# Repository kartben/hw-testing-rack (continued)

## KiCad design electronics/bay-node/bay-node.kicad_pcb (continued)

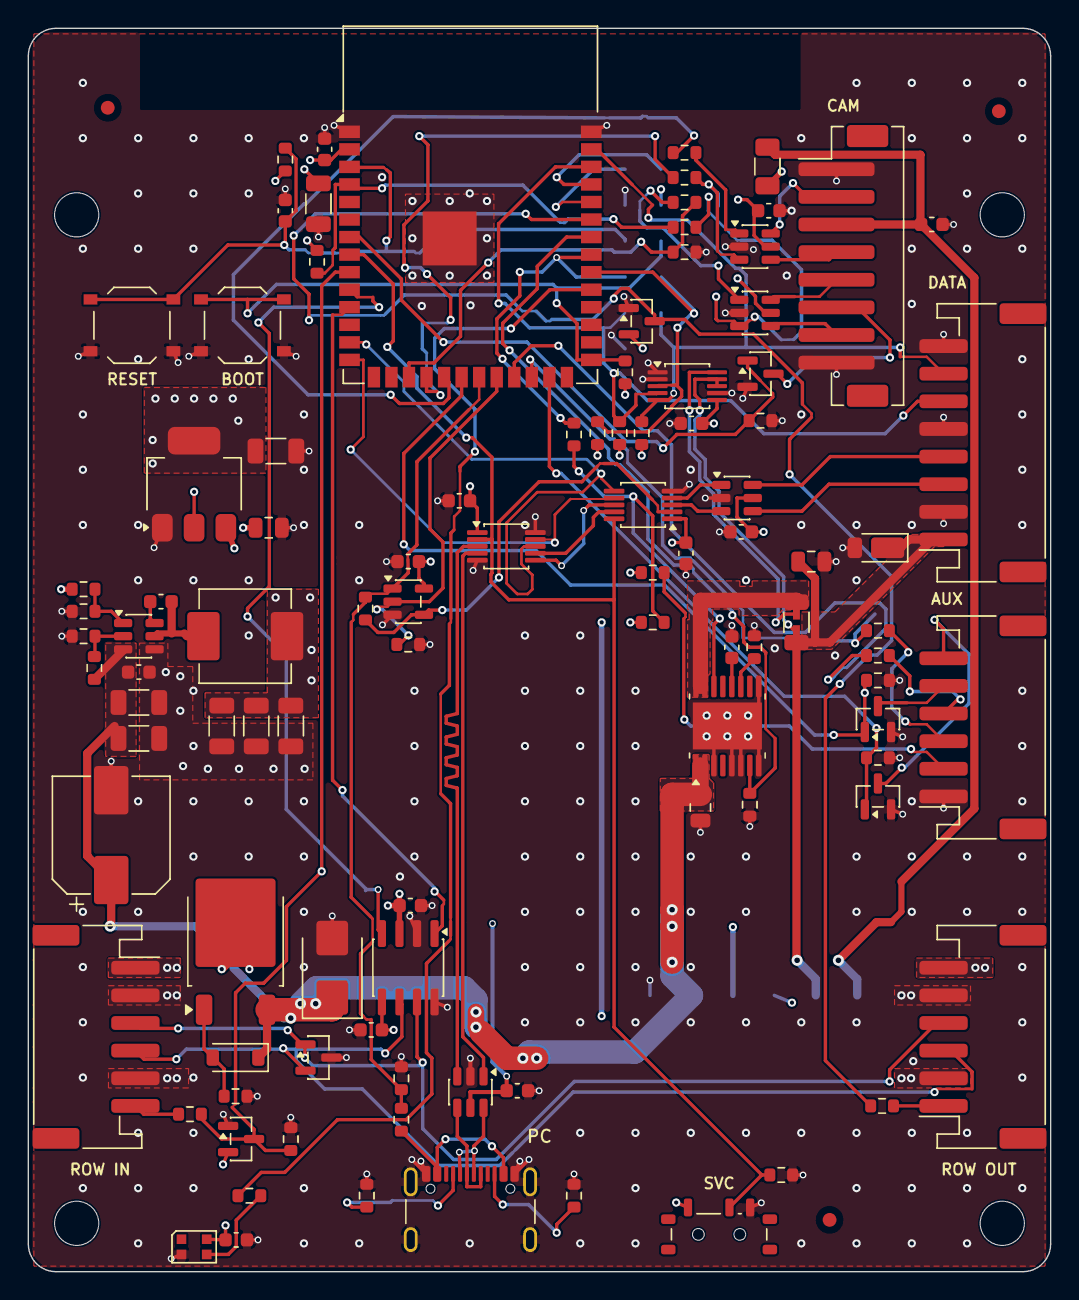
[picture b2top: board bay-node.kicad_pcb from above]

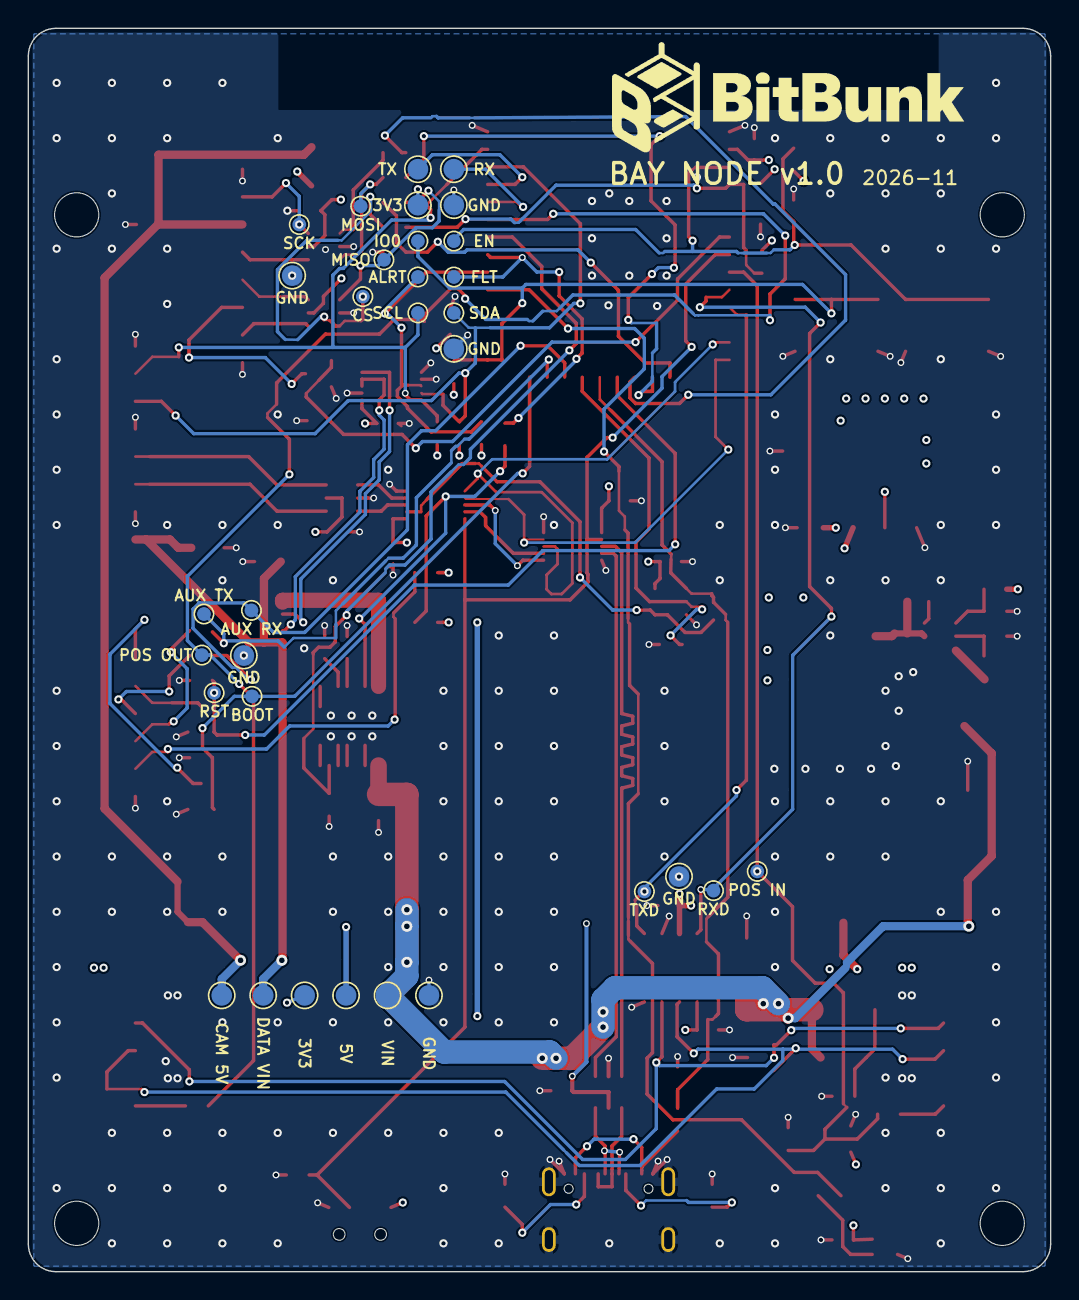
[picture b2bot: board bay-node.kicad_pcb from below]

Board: 4 copper layers, 74.0 x 90.0 mm, 139 parts (32 on the bottom side), 79 nets.

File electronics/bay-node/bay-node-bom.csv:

Designator,Qty,Value,Footprint,MPN,Manufacturer,LCSC,Description,DNP,Alternative,Assembly
C1,1,100u/50V,CP_Elec_8x10,RVT1H101M0810,Honor Elec,C3352,100 µF 50 V aluminium electrolytic,,,
"C2,C3",2,10u,C_1206_3216Metric,CL31A106KBHNNNE,Samsung Electro-Mechanics,C13585,Capacitor 10u 1206,,,
"C4,C5,C14,C16,C17,C18,C19,C22,C23,C24,C25,C26,C27,C28",14,100n,C_0603_1608Metric,CC0603KRX7R9BB104,YAGEO,C14663,Capacitor 100n 0603,,,
"C7,C8,C9,C12,C13",5,22u,C_1206_3216Metric,CL31A226KAHNNNE,Samsung Electro-Mechanics,C12891,Capacitor 22u 1206,,,
C11,1,10u,C_0805_2012Metric,CL21A106KAYNNNE,Samsung Electro-Mechanics,C15850,Capacitor 10u 0805,,,
C15,1,1u,C_0603_1608Metric,CL10A105KB8NNNC,Samsung Electro-Mechanics,C15849,Capacitor 1u 0603,,,
"C20,C21",2,1u,C_0805_2012Metric,CL21B105KBFNNNE,Samsung Electro-Mechanics,C28323,Capacitor 1u 0805,,,
C29,1,22n,C_0603_1608Metric,CL10B223KB8NNNC,Samsung Electro-Mechanics,C21122,Capacitor 22n 0603,,,
D1,1,BZT52C12,D_SOD-123,BZT52C12,CJ,C43491,"12 V zener, P-FET gate clamp",,,
D2,1,SMBJ33A,D_SMB,SMBJ33A,Brightking,C78419,"TVS 33 V stand-off, 600 W (unidirectional)",,,
D4,1,WS2812B-2020-V6,LED_WS2812B-2020_PLCC4_2.0x2.0mm,WS2812B-2020-V6,Worldsemi,C52917434,"addressable RGB LED, 3.3–5.3 V",,WS2812C-2020-V6 (C55109522) is Economic-PCBA capable; check its pinout before swapping,
D5,1,PESD2CAN,SOT-23,"PESD2CAN,215",Nexperia,C75176,"CAN bus ESD protection, 24 V stand-off",,,
"D6,D7",2,BAT54S,SOT-23,BAT54S,hongjiacheng,C7420333,dual Schottky in series: clamps a line to GND and +3V3,,,
D8,1,DFLS260-7,D_PowerDI-123,DFLS260-7,Diodes Inc.,C209346,"60 V 2 A Schottky, 0.62 V at 2 A",,,
F1,1,0.75A,Fuse_1206_3216Metric,SMD1206P075TF,RUILON,C20987,"PTC 0.75 A hold, 1.5 A trip, 1206",,,
J1,1,ROW IN,JST_PH_S6B-PH-SM4-TB_1x06-1MP_P2.00mm_Horizontal,S6B-PH-SM4-TB(LF)(SN),JST,C265405,"JST PH 6-pin, side entry, SMD",,,
J2,1,ROW OUT,JST_PH_S6B-PH-SM4-TB_1x06-1MP_P2.00mm_Horizontal,S6B-PH-SM4-TB(LF)(SN),JST,C265405,"JST PH 6-pin, side entry, SMD",,,
J3,1,PC,USB_C_Receptacle_GCT_USB4105-xx-A_16P_TopMnt_Horizontal,USB4105-GF-A-120,GCT,C5184243,"USB-C receptacle, USB 2.0, 16 pins, 5 A on VBUS",,,
J5,1,AUX,JST_PH_S6B-PH-SM4-TB_1x06-1MP_P2.00mm_Horizontal,S6B-PH-SM4-TB(LF)(SN),JST,C265405,"JST PH 6-pin, side entry, SMD",,,
J6,1,CAM,JST_PH_B8B-PH-SM4-TB_1x08-1MP_P2.00mm_Vertical,B8B-PH-SM4-TB(LF)(SN),JST,C495548,"JST PH 8-pin, vertical, SMD",,,
J7,1,DATA,JST_PH_S8B-PH-SM4-TB_1x08-1MP_P2.00mm_Horizontal,S8B-PH-SM4-TB(LF)(SN),JST,C265121,"JST PH 8-pin, side entry, SMD",,,
L1,1,4.7u,L_Changjiang_FXL0630,IHLP2525CZEK4R7M01,Vishay,C48009678,"4.7 µH, 75 V, 10 A sat (−20 %), 5.5 A heat (ΔT 40 °C), 37 mΩ (40 max), molded",,IHLP2525CZER4R7M01 (C553961): the same part on a 2000-piece reel,
Q1,1,SUD50P06-15(UMW),TO-252-2,SUD50P06-15(UMW),UMW,C7503186,"P-MOSFET 60 V, reverse-polarity protection",,"C7472883 (TECH PUBLIC), C141584 (Vishay)",
"Q2,Q3",2,2N7002,SOT-23,2N7002,CJ,C8545,N-MOSFET 60 V (open-drain AUX outputs),,,
Q4,1,AO3400A,SOT-23,AO3400A,Alpha & Omega Semicon,C20917,"N-MOSFET 30 V 5.7 A, 48 mΩ at 2.5 V (the camera light's low side)",,,
"R1,R2,R4,R13,R26,R27,R36,R39",8,100k,R_0603_1608Metric,0603WAF1003T5E,UNI-ROYAL(Uniroyal Elec),C25803,Resistor 100k 0603,,,
"R3,R6,R7,R11,R17,R18,R20,R28,R30,R37",10,10k,R_0603_1608Metric,0603WAF1002T5E,UNI-ROYAL(Uniroyal Elec),C25804,Resistor 10k 0603,,,
"R5,R12",2,18k,R_0603_1608Metric,0603WAF1802T5E,UNI-ROYAL(Uniroyal Elec),C25810,Resistor 18k 0603,,,
"R8,R31,R32,R33,R34",5,33,R_0603_1608Metric,0603WAF330JT5E,UNI-ROYAL(Uniroyal Elec),C23140,Resistor 33 0603,,,
"R9,R10",2,5.1k,R_0603_1608Metric,0603WAF5101T5E,UNI-ROYAL(Uniroyal Elec),C23186,Resistor 5.1k 0603,,,
R16,1,6.8k,R_0603_1608Metric,0603WAF6801T5E,UNI-ROYAL(Uniroyal Elec),C23212,Resistor 6.8k 0603,,,
R19,1,50m,R_1206_3216Metric_Kelvin,HoLR1206-1W-50mR-1%-75ppm,Milliohm,C601102,50 mΩ 1 % 1 W current shunt,,,
"R21,R22",2,2.2k,R_0603_1608Metric,0603WAF2201T5E,UNI-ROYAL(Uniroyal Elec),C4190,Resistor 2.2k 0603,,,
"R23,R24,R25,R43",4,1k,R_0603_1608Metric,0603WAF1001T5E,UNI-ROYAL(Uniroyal Elec),C21190,Resistor 1k 0603,,,
"R29,R42",2,150k,R_0603_1608Metric,0603WAF1503T5E,UNI-ROYAL(Uniroyal Elec),C22807,Resistor 150k 0603,,,
R35,1,680,R_0603_1608Metric,0603WAF6800T5E,UNI-ROYAL(Uniroyal Elec),C23228,Resistor 680 0603,yes,,
SW1,1,RESET,SW_Push_1P1T_XKB_TS-1187A,TS-1187A-B-A-B,XKB,C318884,tactile switch 5.1 × 5.1 mm,,,
SW2,1,BOOT,SW_Push_1P1T_XKB_TS-1187A,TS-1187A-B-A-B,XKB,C318884,tactile switch 5.1 × 5.1 mm,,,
SW3,1,SERVICE,SW_SPDT_Shouhan_MSK12C02,MSK12C02,SHOU HAN,C431540,"SPDT slide switch, side actuated",,,
U1,1,LMR51625YDDCR,TSOT-23-6,LMR51625YDDCR,Texas Instruments,C44991044,"4.3–60 V 2.5 A synchronous buck, 1.1 MHz, PFM + spread spectrum",,"LMR51625YFDDCR (C45262768): same, forced PWM, no spread spectrum; LMR51635YDDCR (C45262770): 3.5 A, 3.3 µH",
U2,1,AP2114H-3.3TRG1,SOT-223-3_TabPin2,AP2114H-3.3TRG1,Diodes Incorporated,C150716,"3.3 V 1 A LDO, 450 mV dropout at 1 A, SOT-223",,,
U3,1,ESP32-S3-WROOM-1-N8R8,ESP32-S3-WROOM-1_NoEPVias,ESP32-S3-WROOM-1-N8R8,Espressif,C2913201,"ESP32-S3 module, 8 MB flash, 8 MB octal PSRAM, PCB antenna, USB OTG (full speed)",,,
"U4,U8,U12,U13",4,USBLC6-2SC6,SOT-23-6,USBLC6-2SC6,STMicroelectronics,C7519,USB ESD protection,,C2687116 (UMW clone),
U5,1,MUX_PC,MSOP-10_3x3mm_P0.5mm,FSUSB42MUX,onsemi,C11355,USB 2.0 HS 2:1 switch,,,
U6,1,MUX_DUT,MSOP-10_3x3mm_P0.5mm,FSUSB42MUX,onsemi,C11355,USB 2.0 HS 2:1 switch,,,
U7,1,SN74LVC1G32DBVR,SOT-23-5,SN74LVC1G32DBVR,Texas Instruments,C10096,single 2-input OR,,,
U9,1,TPS26600PWPR,HTSSOP-16-1EP_4.4x5mm_P0.65mm_EP3.4x5mm_Mask2.66x2.46mm,TPS26600PWPR,Texas Instruments,C544399,4.2–60 V 2.23 A eFuse,,,
U10,1,INA226AIDGSR,TSSOP-10_3x3mm_P0.5mm,INA226AIDGSR,Texas Instruments,C49851,"36 V current/voltage/power monitor, I2C",,,
U11,1,TJA1462AT,SOIC-8_3.9x4.9mm_P1.27mm,TJA1462AT/0Z,NXP Semiconductors,C3234095,"CAN FD SIC transceiver, VCC 5 V, VIO 2.95–5.5 V, bus pins −36/+40 V (MCP2562 pinout)",,"Same pinout: TI TCAN1462VDRQ1 (C7399456, SIC, bus pins ±58 V; LCSC stock 0 on 2026-10-18 and 19) or TCAN1044AVDRQ1 (C3234993, no SIC, ±58 V)",

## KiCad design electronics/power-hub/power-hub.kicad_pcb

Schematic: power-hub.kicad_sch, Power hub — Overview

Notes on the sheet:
USB-C PD input
Four eFused row outputs (6-pin JST PH)
Rack controller: supplies, ESP32-S3, USB-C,
CAN
+3V3
VRACK
ADC_IMON_A/B/C/D, CAN_H/L, FLT_A/B/C/D, POS_A/B/C/D,
ROW_EN_A/B/C/D, VRACK
I2C_PU, PD_INT/SCL/SDA, VBUS_SENSE, VRACK
Power hub v1.0 — USB-C PD in (CH224A: 9 V, then 20 V or 28 V EPR as the controller asks) = VRACK → 4 × TPS26600 eFuse (1.6 A) → 6-pin JST PH rows A–D. Rack controller: ESP32-S3-MINI-1 on VBUS, TJA1462AT (CAN master, star bus, both terminations here), POS token per row. Rows are OFF without firmware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

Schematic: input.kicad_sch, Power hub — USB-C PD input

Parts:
C1, C9: 10u; C_1206_3216Metric; MPN CL31A106KBHNNNE; LCSC C13585
C2, C3, C10: 100n; C_0603_1608Metric; MPN CC0603KRX7R9BB104; LCSC C14663
C4: 1u; C_0805_2012Metric; MPN CL21B105KBFNNNE; LCSC C28323
C8: 100u/50V; CP_Elec_8x10; MPN RVT1H101M0810; LCSC C3352
D1: SMAJ30A; D_SMA; MPN SMAJ30A; LCSC C113965
D3: PD; LED_Kingbright_KPA-3010_3x2x1mm; MPN KPA-3010CGCK; LCSC C598310
J1: PD IN; USB_C_Receptacle_GCT_USB4105-xx-A_16P_TopMnt_Horizontal; MPN USB4105-GF-A-120; LCSC C5184243
R2: 1k; R_0603_1608Metric; MPN 0603WAF1001T5E; LCSC C21190
R3: 100k; R_0603_1608Metric; MPN 0603WAF1003T5E; LCSC C25803
R4, R11: 10k; R_0603_1608Metric; MPN 0603WAF1002T5E; LCSC C25804
R5: 56; R_0603_1608Metric; MPN 0603WAF560JT5E; LCSC C25196
R6: 6.8k; R_0603_1608Metric; MPN 0603WAF6801T5E; LCSC C23212
R13, R14: 5.1k; R_0603_1608Metric; MPN 0603WAF5101T5E; LCSC C23186
TP23: PD_VHV; TestPoint_Pad_D1.5mm; MPN test pad
U1: CH224A; SSOP-10-1EP_3.9x4.9mm_P1mm_EP2.1x3.3mm; MPN CH224A; LCSC C42459160

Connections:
+3V3: R2.1, R11.1; also elsewhere on the board
/Input/PD_CC1: J1.A5 (CC1), U1.7 (CC1)
/Input/PD_CC2: J1.B5 (CC2), U1.6 (CC2)
/Input/PD_CFG1: R6.1, U1.9 (CFG1)
/Input/PD_LED_A: D3.2 (A), R2.2
/Input/PD_VHV: C4.1, R5.2, TP23.1, U1.1 (VDD), U1.8 (VBUS)
GND: C1.2, C2.2, C3.2, C4.2, C8.2, C9.2, C10.2, D1.2 (A), J1.A1 (GND), J1.A12 (GND), J1.B1 (GND), J1.B12 (GND), J1.SH (SHIELD), R4.2, R6.2, U1.11 (GND); also elsewhere on the board
I2C_PU: R13.1, R14.1; also elsewhere on the board
PD_INT: D3.1 (K), R11.2, U1.10 (PG); also elsewhere on the board
PD_SCL: R14.2, U1.2 (CFG2); also elsewhere on the board
PD_SDA: R13.2, U1.3 (CFG3); also elsewhere on the board
VBUS_SENSE: C3.1, R3.2, R4.1; also elsewhere on the board
VRACK: C1.1, C2.1, C8.1, C9.1, C10.1, D1.1 (K), J1.A4 (VBUS), J1.A9 (VBUS), J1.B4 (VBUS), J1.B9 (VBUS), R3.1, R5.1; also elsewhere on the board

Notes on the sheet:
USB-C PD input (5 A receptacle, CC to the sink controller), TVS; VBUS is VRACK (no input switch)
CH224A USB PD 3.2 sink: 9 V at plug-in (CFG1 6.8k), then 20 V / 28 V EPR as the controller asks over I2C
I2C to the controller, VBUS sense
PD status (front LED): on while the CH224A reports power good (PG low)
U1 is the CH224A (WCH, PD 3.2): CFG1 6.8k asks for 9 V at plug-in and turns its I2C on (0x22); the controller writes 0x0A: 5 = 28 V EPR when offered, else 4 = 20 V (single-byte I2C transfers). CH224 V2.1 lists the source's PDOs (0x60-0x8F) for both parts, readable under 100 W (p. 7): with our 100 W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

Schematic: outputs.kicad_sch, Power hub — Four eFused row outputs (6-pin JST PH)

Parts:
C11, C12, C13, C14, C31, C32, C33, C34: 1u; C_0805_2012Metric; MPN CL21B105KBFNNNE; LCSC C28323
C21, C22, C23, C24: 100n; C_0603_1608Metric; MPN CC0603KRX7R9BB104; LCSC C14663
C61, C62, C63, C64: 47n; C_0603_1608Metric; MPN CL10B473KB8NNNC; LCSC C1622
D11, D12, D13, D14: ON; LED_Kingbright_KPA-3010_3x2x1mm; MPN KPA-3010CGCK; LCSC C598310
D21, D22, D23, D24: FAULT; LED_Kingbright_KPA-3010_3x2x1mm; MPN KPA-3010SURCK; LCSC C4555382
D31, D32, D33, D34: BAT54S; SOT-23; MPN BAT54S; LCSC C7420333
D41, D42, D43, D44: DFLS260-7; D_PowerDI-123; MPN DFLS260-7; LCSC C209346
J2: ROW A; JST_PH_S6B-PH-SM4-TB_1x06-1MP_P2.00mm_Horizontal; MPN S6B-PH-SM4-TB(LF)(SN); LCSC C265405
J3: ROW B; JST_PH_S6B-PH-SM4-TB_1x06-1MP_P2.00mm_Horizontal; MPN S6B-PH-SM4-TB(LF)(SN); LCSC C265405
J4: ROW C; JST_PH_S6B-PH-SM4-TB_1x06-1MP_P2.00mm_Horizontal; MPN S6B-PH-SM4-TB(LF)(SN); LCSC C265405
J5: ROW D; JST_PH_S6B-PH-SM4-TB_1x06-1MP_P2.00mm_Horizontal; MPN S6B-PH-SM4-TB(LF)(SN); LCSC C265405
R21, R22, R23, R24: 7.5k; R_0603_1608Metric; MPN 0603WAF7501T5E; LCSC C23234
R31, R32, R33, R34, R41, R42, R43, R44: 18k; R_0603_1608Metric; MPN 0603WAF1802T5E; LCSC C25810
R51, R52, R53, R54, R61, R62, R63, R64: 1k; R_0603_1608Metric; MPN 0603WAF1001T5E; LCSC C21190
R71, R72, R73, R74, R81, R82, R83, R84, R101, R102, R103, R104: 10k; R_0603_1608Metric; MPN 0603WAF1002T5E; LCSC C25804
R91, R92, R93, R94: 100k; R_0603_1608Metric; MPN 0603WAF1003T5E; LCSC C25803
TP24: ROW_A; TestPoint_Pad_D1.5mm; MPN test pad
TP25: ROW_B; TestPoint_Pad_D1.5mm; MPN test pad
TP26: ROW_C; TestPoint_Pad_D1.5mm; MPN test pad
TP27: ROW_D; TestPoint_Pad_D1.5mm; MPN test pad
U11, U12, U13, U14: TPS26600PWPR; HTSSOP-16-1EP_4.4x5mm_P0.65mm_EP3.4x5mm_Mask2.66x2.46mm; MPN TPS26600PWPR; LCSC C544399

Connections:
+3V3: D31.2 (K), D32.2 (K), D33.2 (K), D34.2 (K), R91.1, R92.1, R93.1, R94.1; also elsewhere on the board
/Outputs/DVDT_A: C21.1, U11.12 (dVdT)
/Outputs/DVDT_B: C22.1, U12.12 (dVdT)
/Outputs/DVDT_C: C23.1, U13.12 (dVdT)
/Outputs/DVDT_D: C24.1, U14.12 (dVdT)
/Outputs/FLTLED_A: D21.2 (A), R51.2
/Outputs/FLTLED_B: D22.2 (A), R52.2
/Outputs/FLTLED_C: D23.2 (A), R53.2
/Outputs/FLTLED_D: D24.2 (A), R54.2
/Outputs/ILIM_A: R21.1, U11.11 (ILIM)
/Outputs/ILIM_B: R22.1, U12.11 (ILIM)
/Outputs/ILIM_C: R23.1, U13.11 (ILIM)
/Outputs/ILIM_D: R24.1, U14.11 (ILIM)
/Outputs/IMON_A: R31.1, R61.1, U11.10 (IMON)
/Outputs/IMON_B: R32.1, R62.1, U12.10 (IMON)
/Outputs/IMON_C: R33.1, R63.1, U13.10 (IMON)
/Outputs/IMON_D: R34.1, R64.1, U14.10 (IMON)
/Outputs/ON_A: D11.2 (A), R41.2
/Outputs/ON_B: D12.2 (A), R42.2
/Outputs/ON_C: D13.2 (A), R43.2
/Outputs/ON_D: D14.2 (A), R44.2
/Outputs/POS_A_CONN: J2.1, R101.2
/Outputs/POS_B_CONN: J3.1, R102.2
/Outputs/POS_C_CONN: J4.1, R103.2
/Outputs/POS_D_CONN: J5.1, R104.2
/Outputs/ROW_A: C31.1, D41.1 (K), J2.6, R41.1, TP24.1, U11.15 (OUT), U11.16 (OUT)
/Outputs/ROW_B: C32.1, D42.1 (K), J3.6, R42.1, TP25.1, U12.15 (OUT), U12.16 (OUT)
/Outputs/ROW_C: C33.1, D43.1 (K), J4.6, R43.1, TP26.1, U13.15 (OUT), U13.16 (OUT)
/Outputs/ROW_D: C34.1, D44.1 (K), J5.6, R44.1, TP27.1, U14.15 (OUT), U14.16 (OUT)
/Outputs/SHDN_A: R71.1, R81.2, U11.7 (~SHDN)
/Outputs/SHDN_B: R72.1, R82.2, U12.7 (~SHDN)
/Outputs/SHDN_C: R73.1, R83.2, U13.7 (~SHDN)
/Outputs/SHDN_D: R74.1, R84.2, U14.7 (~SHDN)
ADC_IMON_A: C61.1, R61.2; also elsewhere on the board
ADC_IMON_B: C62.1, R62.2; also elsewhere on the board
ADC_IMON_C: C63.1, R63.2; also elsewhere on the board
ADC_IMON_D: C64.1, R64.2; also elsewhere on the board
CAN_H: J2.4, J3.4, J4.4, J5.4; also elsewhere on the board
CAN_L: J2.3, J3.3, J4.3, J5.3; also elsewhere on the board
FLT_A: D21.1 (K), R91.2, U11.14 (~FLT); also elsewhere on the board
FLT_B: D22.1 (K), R92.2, U12.14 (~FLT); also elsewhere on the board
FLT_C: D23.1 (K), R93.2, U13.14 (~FLT); also elsewhere on the board
FLT_D: D24.1 (K), R94.2, U14.14 (~FLT); also elsewhere on the board
GND: C11.2, C12.2, C13.2, C14.2, C21.2, C22.2, C23.2, C24.2, C31.2, C32.2, C33.2, C34.2, C61.2, C62.2, C63.2, C64.2, D11.1 (K), D12.1 (K), D13.1 (K), D14.1 (K), D31.1 (A), D32.1 (A), D33.1 (A), D34.1 (A), D41.2 (A), D42.2 (A), D43.2 (A), D44.2 (A), J2.2, J2.5, J3.2, J3.5, J4.2, J4.5, J5.2, J5.5, R21.2, R22.2, R23.2, R24.2, R31.2, R32.2, R33.2, R34.2, R71.2, R72.2, R73.2, R74.2, U11.3 (UVLO), U11.5 (OVP), U11.6 (MODE), U11.8 (RTN), U11.9 (GND), U11.17 (RTN), U12.3 (UVLO), U12.5 (OVP), U12.6 (MODE), U12.8 (RTN), U12.9 (GND), U12.17 (RTN), U13.3 (UVLO), U13.5 (OVP), U13.6 (MODE), U13.8 (RTN), U13.9 (GND), U13.17 (RTN), U14.3 (UVLO), U14.5 (OVP), U14.6 (MODE), U14.8 (RTN), U14.9 (GND), U14.17 (RTN); also elsewhere on the board
POS_A: D31.3 (COM), R101.1; also elsewhere on the board
POS_B: D32.3 (COM), R102.1; also elsewhere on the board
POS_C: D33.3 (COM), R103.1; also elsewhere on the board
POS_D: D34.3 (COM), R104.1; also elsewhere on the board
ROW_EN_A: R51.1, R81.1; also elsewhere on the board
ROW_EN_B: R52.1, R82.1; also elsewhere on the board
ROW_EN_C: R53.1, R83.1; also elsewhere on the board
ROW_EN_D: R54.1, R84.1; also elsewhere on the board
VRACK: C11.1, C12.1, C13.1, C14.1, U11.1 (IN), U11.2 (IN), U12.1 (IN), U12.2 (IN), U13.1 (IN), U13.2 (IN), U14.1 (IN), U14.2 (IN); also elsewhere on the board

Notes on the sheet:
Row A: TPS26600 eFuse 1.6 A, enable, ON / FAULT LEDs, 6-pin JST PH
Row B: TPS26600 eFuse 1.6 A, enable, ON / FAULT LEDs, 6-pin JST PH
Row C: TPS26600 eFuse 1.6 A, enable, ON / FAULT LEDs, 6-pin JST PH
Row D: TPS26600 eFuse 1.6 A, enable, ON / FAULT LEDs, 6-pin JST PH
TPS26600: I_LIM ≈ 12 A·kΩ / R_ILIM → 7.5k ≈ 1.6 A (JST PH: 2 A per contact). t_dVdT = 8e3 · V_IN · C_dVdT → 100 nF ≈ 16 ms at 20 V, 22 ms at 28 V. A row of four nodes (≈ 450 µF) then charges at C / (8e3 · C_dVdT) ≈ 0.56 A (≤ 1.3 A at the corners with the nodes' load), under the 1.6 A limit. The eFu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

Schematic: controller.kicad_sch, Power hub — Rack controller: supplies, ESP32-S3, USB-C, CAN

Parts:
C104, C105: 10u; C_1206_3216Metric; MPN CL31A106KBHNNNE; LCSC C13585
C106, C107, C114, C116, C117: 100n; C_0603_1608Metric; MPN CC0603KRX7R9BB104; LCSC C14663
C108, C109, C110, C112, C113: 22u; C_1206_3216Metric; MPN CL31A226KAHNNNE; LCSC C12891
C111: 1u; C_0805_2012Metric; MPN CL21B105KBFNNNE; LCSC C28323
C115, C120: 1u; C_0603_1608Metric; MPN CL10A105KB8NNNC; LCSC C15849
C118, C119: 47n; C_0603_1608Metric; MPN CL10B473KB8NNNC; LCSC C1622
D4, D5: B5819W SL; D_SOD-123; MPN B5819W SL; LCSC C8598
D8: CTL; LED_Kingbright_KPA-3010_3x2x1mm; MPN KPA-3010CGCK; LCSC C598310
D9: PESD2CAN,215; SOT-23; MPN PESD2CAN,215; LCSC C75176
FID1, FID2, FID3: fiducial; Fiducial_1mm_Mask2mm; MPN fiducial
H1, H2, H3, H4: M3; MountingHole_3.2mm_M3; MPN M3 mounting hole
J6: USB; USB_C_Receptacle_GCT_USB4105-xx-A_16P_TopMnt_Horizontal; MPN USB4105-GF-A-120; LCSC C5184243
L1: 4.7u; L_Changjiang_FXL0630; MPN IHLP2525CZEK4R7M01; LCSC C48009678
R205: 39k; R_0603_1608Metric; MPN 0603WAF3902T5E; LCSC C23153
R206, R208: 18k; R_0603_1608Metric; MPN 0603WAF1802T5E; LCSC C25810
R207: 100k; R_0603_1608Metric; MPN 0603WAF1003T5E; LCSC C25803
R209, R210: 10k; R_0603_1608Metric; MPN 0603WAF1002T5E; LCSC C25804
R211: 1k; R_0603_1608Metric; MPN 0603WAF1001T5E; LCSC C21190
R212, R213, R214: 5.1k; R_0603_1608Metric; MPN 0603WAF5101T5E; LCSC C23186
R215, R216, R217, R218: 56; R_0603_1608Metric; MPN 0603WAF560JT5E; LCSC C25196
SW1: RESET; SW_Push_1P1T_XKB_TS-1187A; MPN TS-1187A-B-A-B; LCSC C318884
SW2: BOOT; SW_Push_1P1T_XKB_TS-1187A; MPN TS-1187A-B-A-B; LCSC C318884
TP1: U0TX; TestPoint_Pad_D1.5mm; MPN test pad
TP2: U0RX; TestPoint_Pad_D1.5mm; MPN test pad
TP3, TP7, TP20, TP38: GND; TestPoint_Pad_D1.5mm; MPN test pad
TP4: +3V3; TestPoint_Pad_D1.5mm; MPN test pad
TP5: +5V; TestPoint_Pad_D1.5mm; MPN test pad
TP6: VRACK; TestPoint_Pad_D1.5mm; MPN test pad
TP8: EN; TestPoint_Pad_D1.0mm; MPN test pad
TP9: BOOT; TestPoint_Pad_D1.0mm; MPN test pad
TP10: PD_SDA; TestPoint_Pad_D1.0mm; MPN test pad
TP11: PD_SCL; TestPoint_Pad_D1.0mm; MPN test pad
TP12: FLT_A; TestPoint_Pad_D1.0mm; MPN test pad
TP13: ADC_IMON_A; TestPoint_Pad_D1.0mm; MPN test pad
TP14: FLT_B; TestPoint_Pad_D1.0mm; MPN test pad
TP15: ADC_IMON_B; TestPoint_Pad_D1.0mm; MPN test pad
TP16: FLT_C; TestPoint_Pad_D1.0mm; MPN test pad
TP17: ADC_IMON_C; TestPoint_Pad_D1.0mm; MPN test pad
TP18: FLT_D; TestPoint_Pad_D1.0mm; MPN test pad
TP19: ADC_IMON_D; TestPoint_Pad_D1.0mm; MPN test pad
TP21: +5V_BUCK; TestPoint_Pad_D1.5mm; MPN test pad
TP22: USB_VBUS; TestPoint_Pad_D1.5mm; MPN test pad
TP28: PD_INT; TestPoint_Pad_D1.0mm; MPN test pad
TP29: CAN_H; TestPoint_Pad_D1.0mm; MPN test pad
TP30: CAN_L; TestPoint_Pad_D1.0mm; MPN test pad
TP31: CAN_TXD; TestPoint_Pad_D1.0mm; MPN test pad
TP32: CAN_RXD; TestPoint_Pad_D1.0mm; MPN test pad
TP33: ROW_EN_A; TestPoint_Pad_D1.0mm; MPN test pad
TP34: ROW_EN_B; TestPoint_Pad_D1.0mm; MPN test pad
TP35: ROW_EN_C; TestPoint_Pad_D1.0mm; MPN test pad
TP36: ROW_EN_D; TestPoint_Pad_D1.0mm; MPN test pad
TP37: VBUS_SENSE; TestPoint_Pad_D1.0mm; MPN test pad
U2: LMR51625YDDCR; TSOT-23-6; MPN LMR51625YDDCR; LCSC C44991044
U3: AP2112K-3.3TRG1; SOT-23-5; MPN AP2112K-3.3TRG1; LCSC C51118
U4: ESP32-S3-MINI-1-N8; ESP32-S2-MINI-1; MPN ESP32-S3-MINI-1-N8; LCSC C2913206
U5: USBLC6-2SC6; SOT-23-6; MPN USBLC6-2SC6; LCSC C7519
U6: TJA1462AT; SOIC-8_3.9x4.9mm_P1.27mm; MPN TJA1462AT/0Z; LCSC C3234095

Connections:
+3V3: C112.1, C113.1, C114.1, C117.1, R209.1, R210.1, TP4.1, U3.5 (VOUT), U4.3 (3V3), U6.5 (Vio); also elsewhere on the board
+5V: C111.1, C116.1, D4.1 (K), D5.1 (K), TP5.1, U3.1 (VIN), U3.3 (EN), U6.3 (VDD)
/Controller/+5V_BUCK: C108.1, C109.1, C110.1, D4.2 (A), L1.2, R207.1, TP21.1
/Controller/BOOT: R210.2, SW2.1, TP9.1, U4.4 (IO0)
/Controller/BUCK_CB: C107.1, U2.6 (CB)
/Controller/BUCK_EN: R205.2, R206.1, U2.2 (EN)
/Controller/BUCK_FB: R207.2, R208.1, U2.1 (FB)
/Controller/BUCK_SW: C107.2, L1.1, U2.5 (SW)
/Controller/CAN_RXD: TP32.1, U4.12 (IO8), U6.4 (RXD)
/Controller/CAN_STB: R214.1, U4.13 (IO9), U6.8 (STBY)
/Controller/CAN_TERM1: C118.1, R215.2, R216.1
/Controller/CAN_TERM2: C119.1, R217.2, R218.1
/Controller/CAN_TXD: TP31.1, U4.11 (IO7), U6.1 (TXD)
/Controller/CTL_LED: R211.1, U4.31 (IO35)
/Controller/CTL_LED_A: D8.2 (A), R211.2
/Controller/EN: C115.1, R209.2, SW1.1, TP8.1, U4.45 (EN)
/Controller/U0RX: TP2.1, U4.40 (RXD0)
/Controller/U0TX: TP1.1, U4.39 (TXD0)
/Controller/USB_CC1: J6.A5 (CC1), R212.1
/Controller/USB_CC2: J6.B5 (CC2), R213.1
/Controller/USB_CONN_DN: J6.A7 (D-), J6.B7 (D-), U5.4 (I/O2)
/Controller/USB_CONN_DP: J6.A6 (D+), J6.B6 (D+), U5.6 (I/O1)
/Controller/USB_DN: U4.23 (USB_D-), U5.3 (I/O2)
/Controller/USB_DP: U4.24 (USB_D+), U5.1 (I/O1)
/Controller/USB_VBUS: C120.1, D5.2 (A), J6.A4 (VBUS), J6.A9 (VBUS), J6.B4 (VBUS), J6.B9 (VBUS), TP22.1, U5.5 (VBUS)
ADC_IMON_A: TP13.1, U4.5 (IO1); also elsewhere on the board
ADC_IMON_B: TP15.1, U4.6 (IO2); also elsewhere on the board
ADC_IMON_C: TP17.1, U4.8 (IO4); also elsewhere on the board
ADC_IMON_D: TP19.1, U4.9 (IO5); also elsewhere on the board
CAN_H: D9.1 (K), R215.1, R217.1, TP29.1, U6.7 (CANH); also elsewhere on the board
CAN_L: D9.2 (K), R216.2, R218.2, TP30.1, U6.6 (CANL); also elsewhere on the board
FLT_A: TP12.1, U4.22 (IO18); also elsewhere on the board
FLT_B: TP14.1, U4.25 (IO21); also elsewhere on the board
FLT_C: TP16.1, U4.27 (IO47); also elsewhere on the board
FLT_D: TP18.1, U4.28 (IO33); also elsewhere on the board
GND: C104.2, C105.2, C106.2, C108.2, C109.2, C110.2, C111.2, C112.2, C113.2, C114.2, C115.2, C116.2, C117.2, C118.2, C119.2, C120.2, D8.1 (K), D9.3 (A), J6.A1 (GND), J6.A12 (GND), J6.B1 (GND), J6.B12 (GND), J6.SH (SHIELD), R206.2, R208.2, R212.2, R213.2, R214.2, SW1.2, SW2.2, TP3.1, TP7.1, TP20.1, TP38.1, U2.4 (GND), U3.2 (GND), U4.1 (GND), U4.2 (GND), U4.42 (GND), U4.43 (GND), U4.46 (GND), U4.47 (GND), U4.48 (GND), U4.49 (GND), U4.50 (GND), U4.51 (GND), U4.52 (GND), U4.53 (GND), U4.54 (GND), U4.55 (GND), U4.56 (GND), U4.57 (GND), U4.58 (GND), U4.59 (GND), U4.60 (GND), U4.61 (GND), U4.62 (GND), U4.63 (GND), U4.64 (GND), U4.65 (GND), U5.2 (GND), U6.2 (VSS); also elsewhere on the board
I2C_PU: U4.38 (IO42); also elsewhere on the board
PD_INT: TP28.1, U4.35 (IO39); also elsewhere on the board
PD_SCL: TP11.1, U4.36 (IO40); also elsewhere on the board
PD_SDA: TP10.1, U4.37 (IO41); also elsewhere on the board
POS_A: U4.14 (IO10); also elsewhere on the board
POS_B: U4.15 (IO11); also elsewhere on the board
POS_C: U4.16 (IO12); also elsewhere on the board
POS_D: U4.17 (IO13); also elsewhere on the board
ROW_EN_A: TP33.1, U4.18 (IO14); also elsewhere on the board
ROW_EN_B: TP34.1, U4.19 (IO15); also elsewhere on the board
ROW_EN_C: TP35.1, U4.20 (IO16); also elsewhere on the board
ROW_EN_D: TP36.1, U4.21 (IO17); also elsewhere on the board
VBUS_SENSE: TP37.1, U4.10 (IO6); also elsewhere on the board
VRACK: C104.1, C105.1, C106.1, R205.1, TP6.1, U2.3 (VIN); also elsewhere on the board

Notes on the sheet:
5 V buck: LMR51625 (2.5 A; the controller takes < 0.7 A) and 4.7 µH, as the bay node (TI SLUSF64B table 8-1), from VRACK
5 V for the controller: the buck or the console USB-C (diode OR), 3.3 V low-dropout LDO
ESP32-S3-MINI-1 (antenna at the board's rear edge: no copper under it, either layer)
USB-C: the controller's console / firmware (native USB), and its 5 V without a PD charger
CAN: TJA1462AT, star bus (all row ports in parallel), both terminations here
Mounting (M3, on the power box's standoffs)
GPIO: IO1/2/4/5 IMON A–D, IO6 VBUS_SENSE (ADC1) · IO7/8/9 CAN TX/RX/STB · IO10–13 POS A–D · IO14–17 ROW_EN A–D · IO18/21/47/33 FLT A–D · IO39 PD_INT, IO40/41 PD_SCL/SDA, IO42 I2C_PU · IO35 CTL LED · IO19/20 USB. Strapping IO3/45/46 unused. Termination: two split 2 × 56 Ω + 47 nF (56 Ω in all) at th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

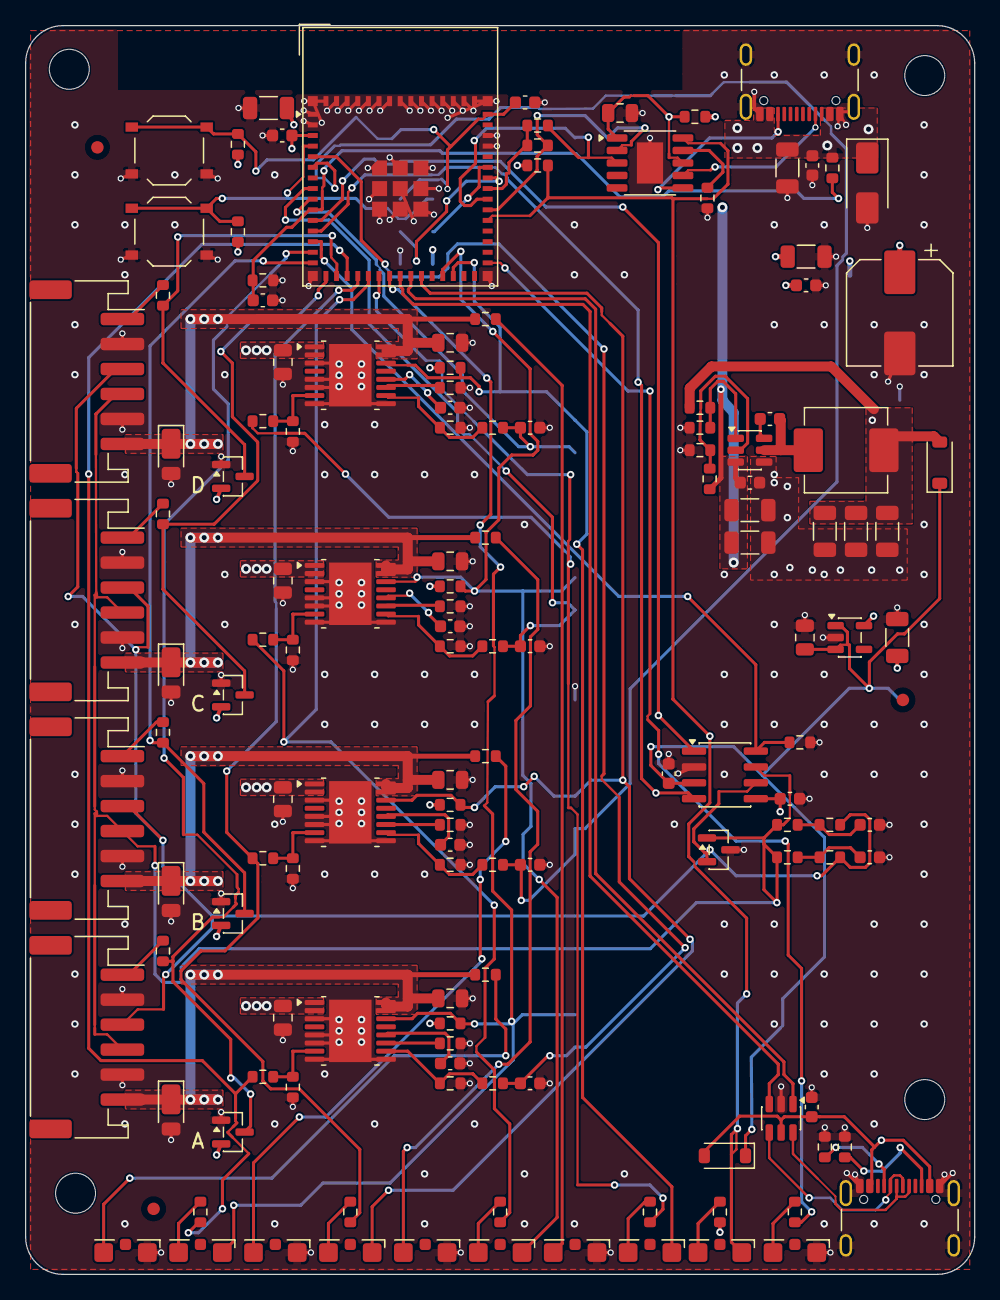
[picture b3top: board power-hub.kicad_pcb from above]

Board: 4 copper layers, 76.0 x 100.0 mm, 184 parts (38 on the bottom side), 87 nets.

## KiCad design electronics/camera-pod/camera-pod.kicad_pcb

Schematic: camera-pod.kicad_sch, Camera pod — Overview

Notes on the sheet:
Lead, camera header, 3.3 V, light
Camera pod v1.0 — PH 8 lead from the bay node's J6, 1 × 6 header for the Arducam Mega's cable, AP2114H 3.3 V for the camera, four white 2835 LEDs switched by the node (LED_K). Lead pinout here: 1 GND · 2 CS · 3 LED_K · 4 MISO · 5 MOSI · 6 CAM_5V · 7 SCK · 8 GND (the node's J6 mirrored: one 'Same di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

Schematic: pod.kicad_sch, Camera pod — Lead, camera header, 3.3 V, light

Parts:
C1: 10u; C_0805_2012Metric; MPN CL21A106KAYNNNE; LCSC C15850
C2: 22u; C_1206_3216Metric; MPN CL31A226KAHNNNE; LCSC C12891
C3: 100n; C_0603_1608Metric; MPN CC0603KRX7R9BB104; LCSC C14663
D1, D2, D3, D4: XL-2835UWC-02; LED_PLCC_2835; MPN XL-2835UWC-02; LCSC C2843876
FID1, FID2, FID3: fiducial; Fiducial_1mm_Mask2mm; MPN fiducial
H1, H2: PT2.6; MountingHole_2.7mm_M2.5; MPN M2.5 / PT 2.6 mounting hole
J1: LEAD; JST_PH_S8B-PH-SM4-TB_1x08-1MP_P2.00mm_Horizontal; MPN S8B-PH-SM4-TB(LF)(SN); LCSC C265121
J2: MEGA; PinHeader_1x06_P2.54mm_Vertical_SMD_Pin1Right; MPN HX PZ2.54-1x6P TP-YQ; LCSC C41417363
R1, R2, R3, R4: 100; R_0805_2012Metric; MPN 0805W8F1000T5E; LCSC C17408
TP1, TP4: GND; TestPoint_Pad_D1.5mm; MPN test pad
TP2: CAM_5V; TestPoint_Pad_D1.5mm; MPN test pad
TP3: +3V3; TestPoint_Pad_D1.5mm; MPN test pad
TP5: SCK; TestPoint_Pad_D1.0mm; MPN test pad
TP6: MOSI; TestPoint_Pad_D1.0mm; MPN test pad
TP7: MISO; TestPoint_Pad_D1.0mm; MPN test pad
TP8: CS; TestPoint_Pad_D1.0mm; MPN test pad
TP9: LED_K; TestPoint_Pad_D1.0mm; MPN test pad
U1: AP2114H-3.3TRG1; SOT-223-3_TabPin2; MPN AP2114H-3.3TRG1; LCSC C150716

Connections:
+3V3: C2.1, C3.1, J2.1, TP3.1, U1.2 (VO)
/Pod/CAM_5V: C1.1, J1.6, R1.1, R2.1, R3.1, R4.1, TP2.1, U1.3 (VI)
/Pod/CS: J1.2, J2.6, TP8.1
/Pod/LED_A1: D1.2 (A), R1.2
/Pod/LED_A2: D2.2 (A), R2.2
/Pod/LED_A3: D3.2 (A), R3.2
/Pod/LED_A4: D4.2 (A), R4.2
/Pod/LED_K: D1.1 (K), D2.1 (K), D3.1 (K), D4.1 (K), J1.3, TP9.1
/Pod/MISO: J1.4, J2.4, TP7.1
/Pod/MOSI: J1.5, J2.5, TP6.1
/Pod/SCK: J1.7, J2.3, TP5.1
GND: C1.2, C2.2, C3.2, J1.1, J1.8, J2.2, TP1.1, TP4.1, U1.1 (GND)

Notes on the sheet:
Lead from the bay node's J6 (JST PH 8, side entry)
The Arducam Mega's cable (1 × 6, 2.54 mm, its own order) and its 3.3 V
Light: four white LEDs, 100 Ω each from CAM_5V, cathodes to LED_K (the node's low side)
Test pads (bottom side, labelled): no short to GND, then CAM_5V and 3.3 V at power-up
J1 is the bay node's J6 mirrored: a 'Same direction' PH 8 lead (pin n to pin 9−n) joins them. J2 follows the Mega's own pin order; the names are on the silkscreen, its cable plugs on by name. The Mega from 3.3 V (U1, ≈ 0.5 W at its 317 mA max, Arducam): its MISO is 3.3 V. LEDs 18–26 mA each (100 Ω 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

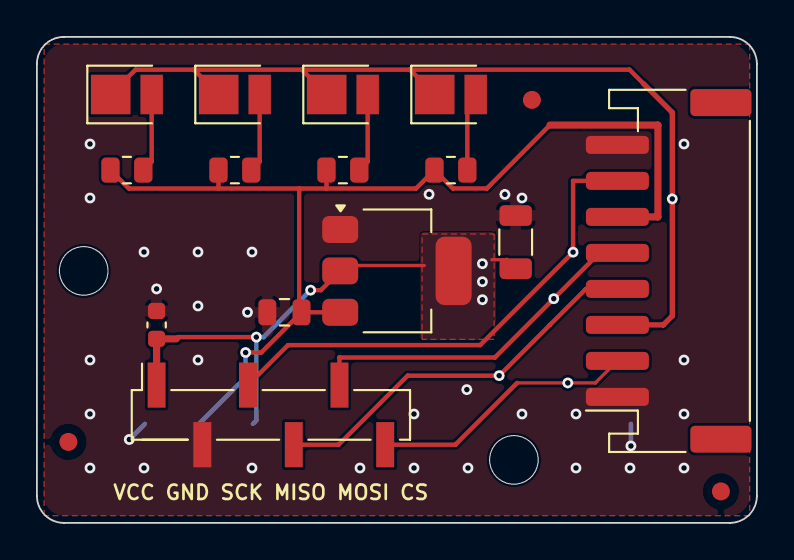
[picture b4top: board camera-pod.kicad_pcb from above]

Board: 2 copper layers, 40.0 x 27.0 mm, 28 parts (9 on the bottom side), 12 nets.

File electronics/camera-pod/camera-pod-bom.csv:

Designator,Qty,Value,Footprint,MPN,Manufacturer,LCSC,Description,DNP,Alternative,Assembly
C1,1,10u,C_0805_2012Metric,CL21A106KAYNNNE,Samsung Electro-Mechanics,C15850,Capacitor 10u 0805,,,
C2,1,22u,C_1206_3216Metric,CL31A226KAHNNNE,Samsung Electro-Mechanics,C12891,Capacitor 22u 1206,,,
C3,1,100n,C_0603_1608Metric,CC0603KRX7R9BB104,YAGEO,C14663,Capacitor 100n 0603,,,
"D1,D2,D3,D4",4,XL-2835UWC-02,LED_PLCC_2835,XL-2835UWC-02,XINGLIGHT,C2843876,"LED white 6000–7500 K, 2835, 20–33 lm at 60 mA",,,
J1,1,LEAD,JST_PH_S8B-PH-SM4-TB_1x08-1MP_P2.00mm_Horizontal,S8B-PH-SM4-TB(LF)(SN),JST,C265121,"JST PH 8-pin, side entry, SMD",,,
J2,1,MEGA,PinHeader_1x06_P2.54mm_Vertical_SMD_Pin1Right,HX PZ2.54-1x6P TP-YQ,hanxia,C41417363,"pin header 1 × 6, 2.54 mm, SMD",,,
"R1,R2,R3,R4",4,100,R_0805_2012Metric,0805W8F1000T5E,UNI-ROYAL(Uniroyal Elec),C17408,Resistor 100 0805,,,
U1,1,AP2114H-3.3TRG1,SOT-223-3_TabPin2,AP2114H-3.3TRG1,Diodes Incorporated,C150716,"3.3 V 1 A LDO, 450 mV dropout at 1 A, SOT-223",,,

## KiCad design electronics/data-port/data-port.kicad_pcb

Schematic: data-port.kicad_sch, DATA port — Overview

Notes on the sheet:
USB-C source, ESD, lead
DATA port v1.0 — USB-C source (Rp 56k on CC1/CC2), USBLC6 ESD, 8-pin JST PH lead to the bay node's J7. Lead pinout here: 1 INT, 2 SCL, 3 SDA (all three open), 4 GND, 5 D−, 6 D+, 7 GND, 8 VBUS (the node's J7 mirrored: one 'Same direction' PH 8 cable).

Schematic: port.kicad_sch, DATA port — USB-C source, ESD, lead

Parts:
C1: 100n; C_0603_1608Metric; MPN CC0603KRX7R9BB104; LCSC C14663
C2: 10u; C_0805_2012Metric; MPN CL21A106KAYNNNE; LCSC C15850
C3: 100n; C_0402_1005Metric; MPN CL05B104KO5NNNC; LCSC C1525
H1, H2: PT2.6; MountingHole_2.7mm_M2.5; MPN M2.5 / PT 2.6 mounting hole
J1: DATA; USB_C_Receptacle_GCT_USB4105-xx-A_16P_TopMnt_Horizontal; MPN USB4105-GF-A-120; LCSC C5184243
J2: LEAD; JST_PH_S8B-PH-SM4-TB_1x08-1MP_P2.00mm_Horizontal; MPN S8B-PH-SM4-TB(LF)(SN); LCSC C265121
R1, R2: 56k; R_0603_1608Metric; MPN 0603WAF5602T5E; LCSC C23206
TP1, TP3: GND; TestPoint_Pad_D1.5mm; MPN test pad
TP2: VBUS; TestPoint_Pad_D1.5mm; MPN test pad
U1: USBLC6-2SC6; SOT-23-6; MPN USBLC6-2SC6; LCSC C7519

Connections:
/Port/CC1: J1.A5 (CC1), R1.2
/Port/CC2: J1.B5 (CC2), R2.2
/Port/CONN_DN: J1.A7 (D-), J1.B7 (D-), U1.4 (I/O2)
/Port/CONN_DP: J1.A6 (D+), J1.B6 (D+), U1.6 (I/O1)
/Port/LEAD_DN: J2.5, U1.3 (I/O2)
/Port/LEAD_DP: J2.6, U1.1 (I/O1)
/Port/VBUS: C1.1, C2.1, C3.1, J1.A4 (VBUS), J1.A9 (VBUS), J1.B4 (VBUS), J1.B9 (VBUS), J2.8, R1.1, R2.1, TP2.1, U1.5 (VBUS)
GND: C1.2, C2.2, C3.2, J1.A1 (GND), J1.A12 (GND), J1.B1 (GND), J1.B12 (GND), J1.SH (SHIELD), J2.4, J2.7, TP1.1, TP3.1, U1.2 (GND)

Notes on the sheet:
USB-C receptacle (source): Rp 56k on each CC, the shell to GND, 10 µF on VBUS
ESD on the pair, at the receptacle
Lead to the bay node's DATA header (J7): 4 GND, 5 D−, 6 D+, 7 GND, 8 VBUS; 1–3 (INT, I²C) open
Test pads (bottom side, labelled): no short to GND, then VBUS at power-up
Rp 56k to VBUS on CC1 and CC2: 'default USB power', as on the DATA ×4; not 22k (1.5 A): the node's TPS2553D switch (DUT_5V) limits at 1.34–1.52 A. The node turns the board under test on and off. The lead's pinout is the node's J7 mirrored: a 'Same direction' PH 8 cable (pin n to pin 9−n) joins them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

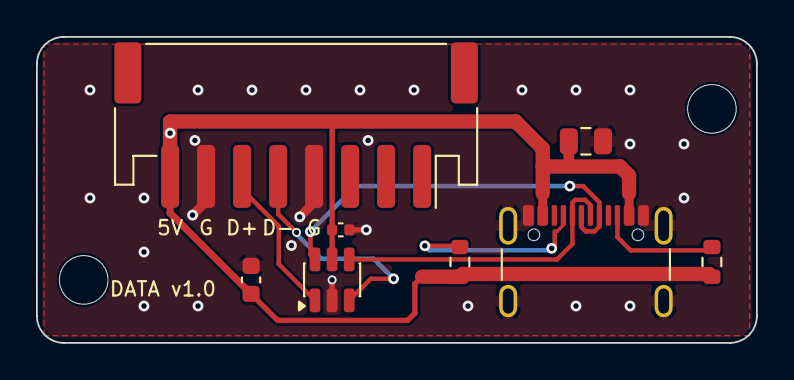
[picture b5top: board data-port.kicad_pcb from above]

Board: 2 copper layers, 40.0 x 17.0 mm, 13 parts (3 on the bottom side), 8 nets.
